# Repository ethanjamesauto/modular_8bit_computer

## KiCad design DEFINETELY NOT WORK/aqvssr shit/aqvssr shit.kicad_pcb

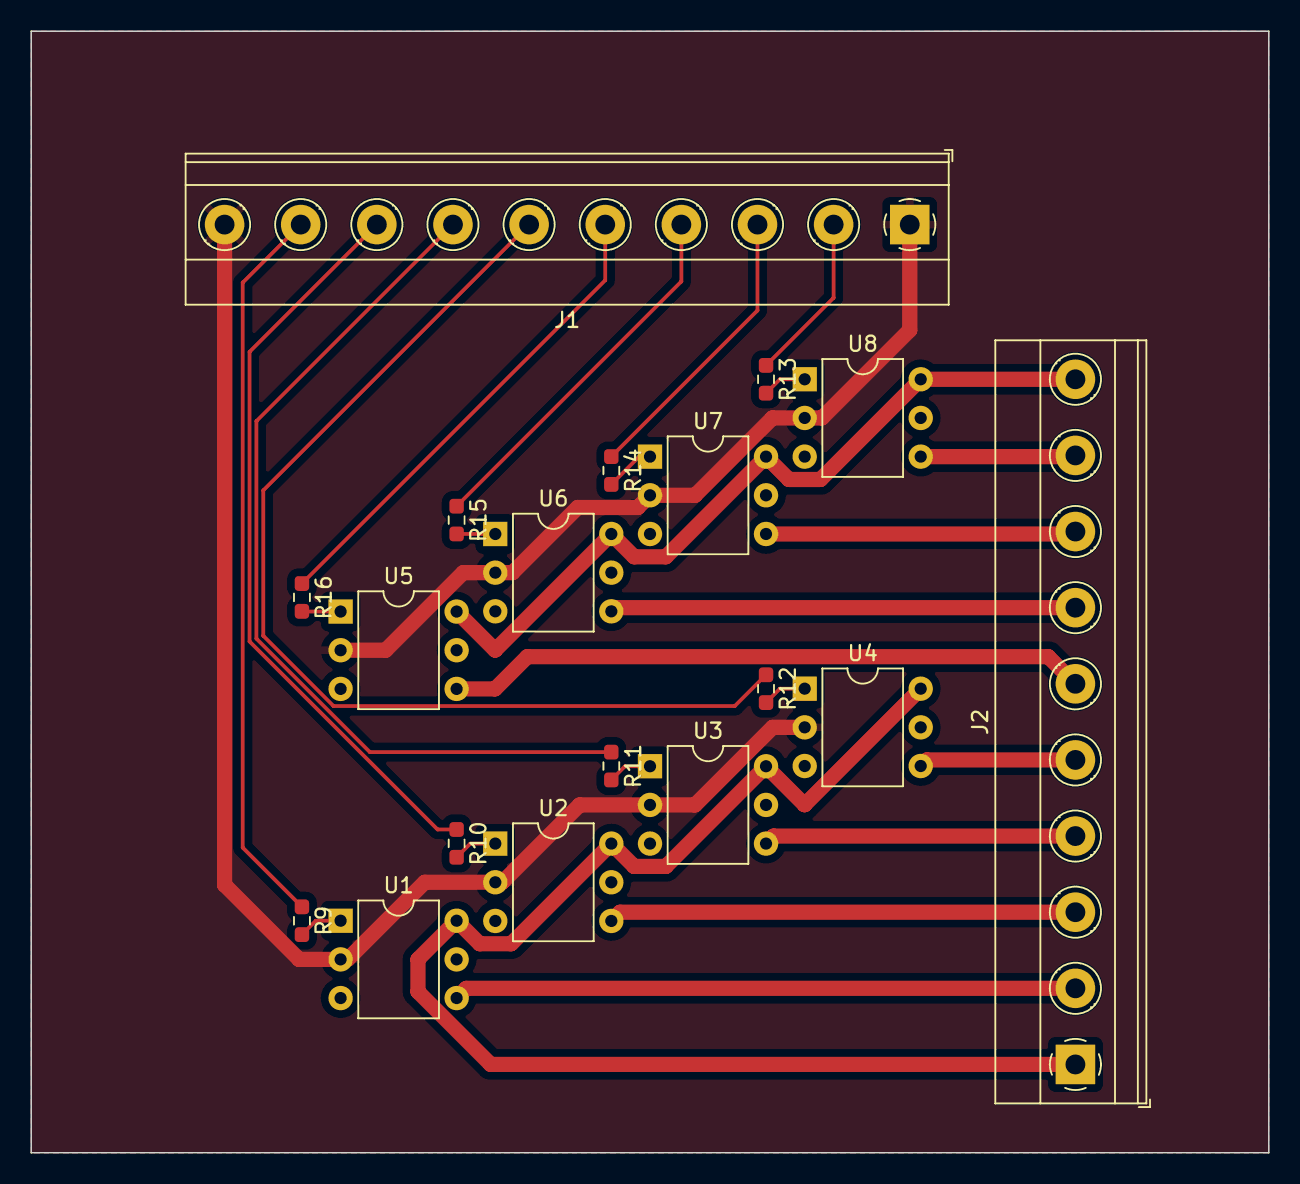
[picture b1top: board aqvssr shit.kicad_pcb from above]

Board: 2 copper layers, 81.3 x 73.7 mm, 18 parts (0 on the bottom side), 26 nets.

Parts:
J1, J2: Conn_01x10_Socket; TerminalBlock_Phoenix_MKDS-1,5-10_1x10_P5.00mm_Horizontal
R9, R10, R11, R12, R13, R14, R15, R16: R; R_0603_1608Metric_Pad0.98x0.95mm_HandSolder
U1, U2, U3, U4, U5, U6, U7, U8: 4N25; DIP-6_W7.62mm

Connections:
/enable_A: J1.9, R9.1
/enable_B: J1.8, R10.1
/enable_C: J1.7, R11.1
/enable_D: J1.6, R12.1
/enable_E: J1.5, R16.1
/enable_F: J1.4, R15.1
/enable_G: J1.3, R14.1
/enable_H: J1.2, R13.1
/hs: J2.1, J2.10, U1.6, U2.6, U3.6, U4.6, U5.6, U6.6, U7.6, U8.6
/ls_A: J2.2, U1.4
/ls_B: J2.3, U2.4
/ls_C: J2.4, U3.4
/ls_D: J2.5, U4.4
/ls_E: J2.6, U5.4
/ls_F: J2.7, U6.4
/ls_G: J2.8, U7.4
/ls_H: J2.9, U8.4
GND: J1.1, J1.10, U1.2, U2.2, U3.2, U4.2, U5.2, U6.2, U7.2, U8.2
unnamed: R9.2, U1.1
unnamed: R10.2, U2.1
unnamed: R11.2, U3.1
unnamed: R12.2, U4.1
unnamed: R13.2, U8.1
unnamed: R14.2, U7.1
unnamed: R15.2, U6.1
unnamed: R16.2, U5.1

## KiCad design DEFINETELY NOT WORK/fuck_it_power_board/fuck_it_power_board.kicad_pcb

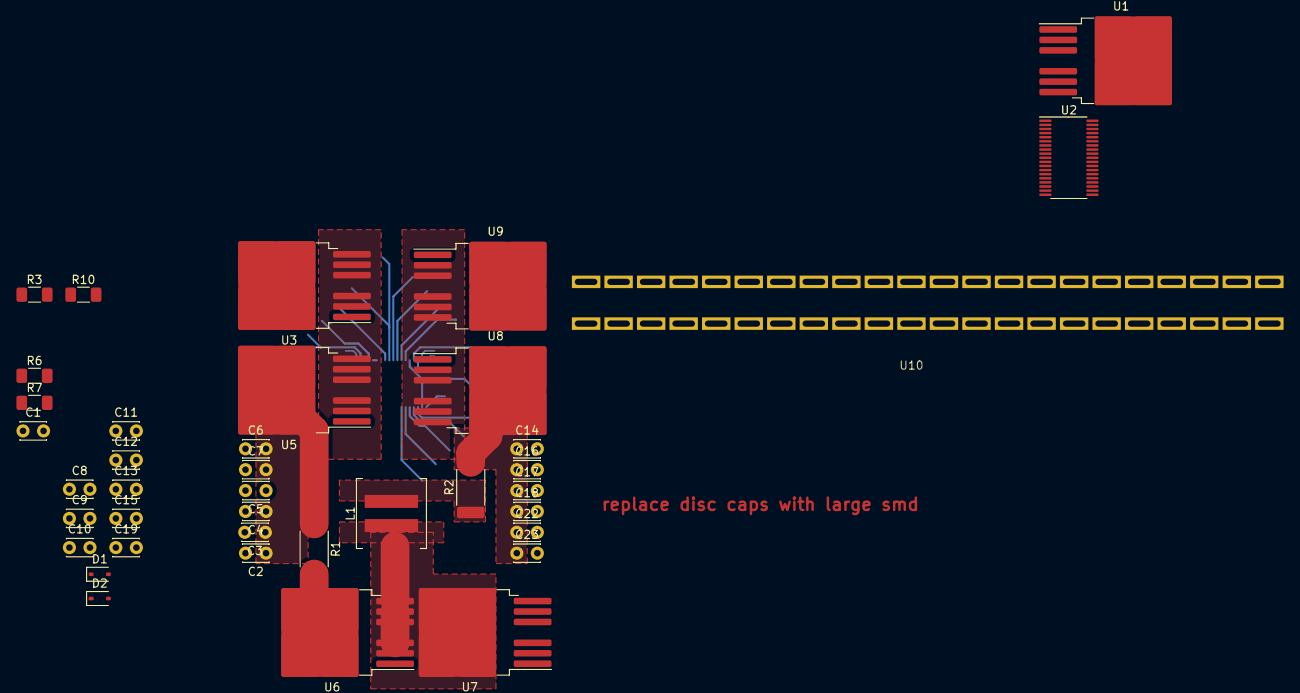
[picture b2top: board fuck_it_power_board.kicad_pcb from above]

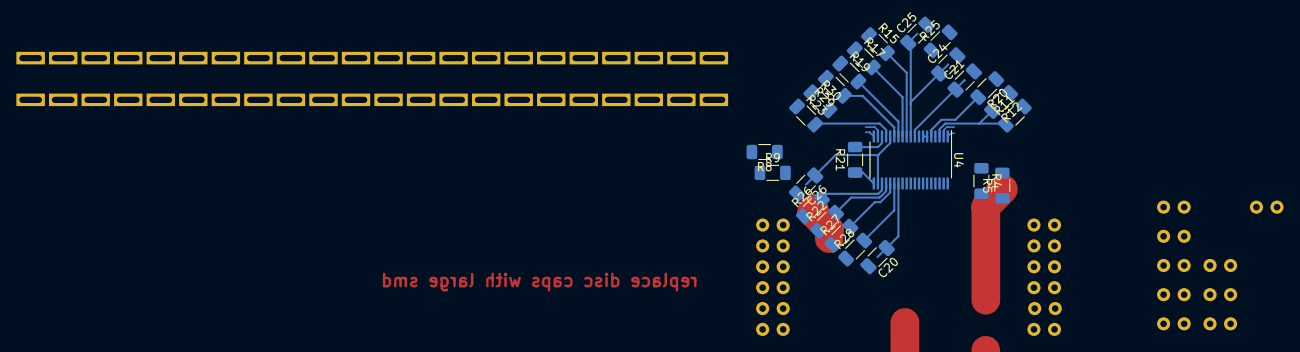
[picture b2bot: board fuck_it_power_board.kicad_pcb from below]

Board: 2 copper layers, 64 parts (25 on the bottom side), 42 nets.

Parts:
C1, C2, C3, C4, C5, C6, C7, C8, C9, C10, C11, C12, C13, C14, C15, C16, C17, C18, C19, C22, C23: C; C_Disc_D3.0mm_W2.0mm_P2.50mm
C20, C21, C24, C25, C26: C; C_1206_3216Metric_Pad1.33x1.80mm_HandSolder
D1: D_TVS; D_SOD-323
D2: D; D_SOD-323
L1: L; L_Coilcraft_XAL7030-472
R1, R2: R; R_2512_6332Metric_Pad1.40x3.35mm_HandSolder
R3, R4, R5, R6, R7, R8, R9, R10, R11, R12, R15, R17, R19, R20, R21, R22, R23, R25, R26, R27, R28, R29, R30: R; R_1206_3216Metric_Pad1.30x1.75mm_HandSolder
U1, U3, U5, U6, U7, U8, U9: TO-263-6
U2, U4: TSSOP-38_4.4x9.7mm_P0.5mm
U10: 50-44A-30

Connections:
/LT8228_BUCK/BG: R7.1, U4.27 (BG)
/LT8228_BUCK/BST: C10.1, D2.1 (K), U4.32 (BST)
/LT8228_BUCK/DG1: D1.2 (A2), R3.2, U3.1, U4.38 (DG1), U5.1
/LT8228_BUCK/DG2: R10.2, U4.35 (DG2), U8.1, U9.1
/LT8228_BUCK/DRVCC: C11.1, D2.2 (A), U4.28 (DRVCC)
/LT8228_BUCK/DRXN: R26.2, U4.22 (DRXN)
/LT8228_BUCK/DS1: D1.1 (A1), U3.2, U3.3, U3.5, U3.6, U3.7, U4.37 (DS1), U5.2, U5.3, U5.5, U5.6, U5.7
/LT8228_BUCK/DS2: U4.34 (DS2), U8.2, U8.3, U8.5, U8.6, U8.7, U9.2, U9.3, U9.5, U9.6, U9.7
/LT8228_BUCK/FB2: R29.1, R30.2, U4.14 (FB2)
/LT8228_BUCK/IGND: R21.1, U4.20 (IGN)
/LT8228_BUCK/IMON1: R20.2, U4.5 (IMON1)
/LT8228_BUCK/IMON2: R19.2, U4.13 (IMON2)
/LT8228_BUCK/INTVCC: C26.1, U4.15 (UV2), U4.21 (INTVCC)
/LT8228_BUCK/ISET1P: C13.1, R15.2, U4.11 (ISET1P)
/LT8228_BUCK/ISET2P: C15.1, R17.2, U4.12 (ISET2P)
/LT8228_BUCK/ISHARE: C19.1, R21.2, U4.17 (ISHARE)
/LT8228_BUCK/POST_RSNS1: C9.1, R1.2, R5.1, U6.4
/LT8228_BUCK/POST_RSNS2: C14.1, C16.1, C17.1, C18.1, C22.1, C23.1, R2.2, R9.1, R29.2, U8.4
/LT8228_BUCK/PRE_RSNS2: L1.2, R2.1, R8.2
/LT8228_BUCK/RT: R23.2, U4.16 (RT)
/LT8228_BUCK/SNS1N: R5.2, U4.2 (SNS1N)
/LT8228_BUCK/SNS1P: R4.1, U4.1 (SNS1P)
/LT8228_BUCK/SNS2N: R9.2, U4.19 (SNS2N)
/LT8228_BUCK/SNS2P: R8.1, U4.18 (SNS2P)
/LT8228_BUCK/SS: C21.1, U4.9 (SS)
/LT8228_BUCK/SW: C10.2, L1.1, U4.30 (SW), U6.2, U6.3, U6.5, U6.6, U6.7, U7.4
/LT8228_BUCK/SYNC: R22.2, U4.23 (SYNC)
/LT8228_BUCK/TG: R6.1, U4.31 (TG)
/LT8228_BUCK/TMR: C20.1, U4.26 (TMR)
/LT8228_BUCK/UV1: R11.1, R12.2, U4.3 (UV1)
/LT8228_BUCK/V1D: C2.1, C3.1, C4.1, C5.2, C6.2, C7.2, R1.1, R4.2, U4.36 (V1D), U5.4
/LT8228_BUCK/VC2: C24.1, C25.1, U4.10 (VC2)
/LT8228_BUCK/~FAULT: R27.2, U4.24 (~FAULT)
/LT8228_BUCK/~REPORT: R28.2, U4.25 (~REPORT)
BUCK_INPUT: C1.1, R11.2, U3.4
GND: C1.2, C2.2, C3.2, C4.2, C5.1, C6.1, C7.1, C8.2, C9.2, C11.2, C12.2, C13.2, C14.2, C15.2, C16.2, C17.2, C18.2, C19.2, C20.2, C21.2, C22.2, C23.2, C25.2, C26.2, R12.1, R15.1, R17.1, R19.1, R20.1, R22.1, R23.1, R25.1, R30.1, U4.4 (FB1), U4.6 (ISET1N), U4.7 (ISET2N), U7.2, U7.3, U7.5, U7.6, U7.7
unnamed: C8.1, R3.1
unnamed: C12.1, R10.1
unnamed: C24.2, R25.2
unnamed: R6.2, U6.1
unnamed: R7.2, U7.1
unnamed: U1.2, U1.3, U1.5, U1.6, U1.7

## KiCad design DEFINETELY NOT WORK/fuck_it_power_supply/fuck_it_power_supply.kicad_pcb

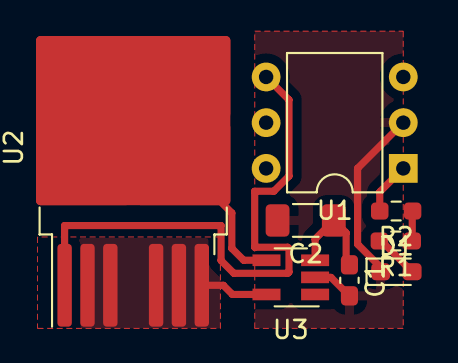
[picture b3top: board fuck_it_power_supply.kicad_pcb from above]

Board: 2 copper layers, 8 parts (0 on the bottom side), 8 nets.

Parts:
C1: C; C_0603_1608Metric_Pad1.08x0.95mm_HandSolder
C2: C; C_1206_3216Metric_Pad1.33x1.80mm_HandSolder
D1: LED; LED_0603_1608Metric_Pad1.05x0.95mm_HandSolder
R1, R2: 470; R_0603_1608Metric_Pad0.98x0.95mm_HandSolder
U1: DIP-6_W7.62mm
U2: TO-263-6
U3: SOT-23-5_HandSoldering

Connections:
/Big Free Load Switch/POWER_INPUT: U2.4, U3.4 (IN+)
/Big Free Load Switch/POWER_OUTPUT: U2.2, U2.3, U2.5, U2.6, U2.7, U3.5 (IN-)
/Big Free Load Switch/close: R1.1, R2.1
/Big Free Load Switch/i_sns_supply: C1.1, C2.1, U3.3 (Vs)
GND: C1.2, C2.2, D1.1 (K), U1.2, U3.2 (GND)
unnamed: D1.2 (A), R1.2
unnamed: R2.2, U1.1
unnamed: U1.4, U2.1

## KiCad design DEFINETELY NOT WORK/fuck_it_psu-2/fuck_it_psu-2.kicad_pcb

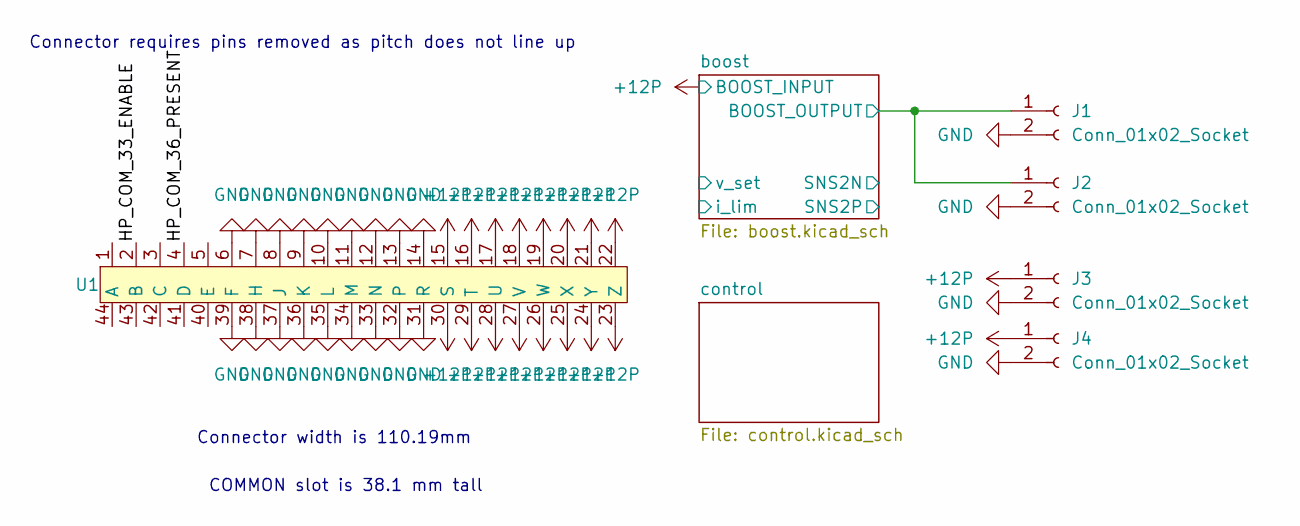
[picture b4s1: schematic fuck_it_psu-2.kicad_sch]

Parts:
J1, J2, J3, J4: Conn_01x02_Socket; PhoenixContact_MSTBA_2,5_2-G_1x02_P5.00mm_Horizontal
U1: 50-44A-30

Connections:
+12P: J3.1, J4.1, U1.15, U1.16, U1.17, U1.18, U1.19, U1.20, U1.21, U1.22, U1.23 (Z), U1.24 (Y), U1.25 (X), U1.26 (W), U1.27 (V), U1.28 (U), U1.29 (T), U1.30 (S); also elsewhere on the board
/HP_COM_33_ENABLE: U1.2
/HP_COM_36_PRESENT: U1.4
/boost/BOOST_OUTPUT: J1.1, J2.1; also elsewhere on the board
GND: J1.2, J2.2, J3.2, J4.2, U1.6, U1.7, U1.8, U1.9, U1.10, U1.11, U1.12, U1.13, U1.14, U1.31 (R), U1.32, U1.33 (N), U1.34 (M), U1.35 (L), U1.36 (K), U1.37 (J), U1.38 (H), U1.39 (F); also elsewhere on the board

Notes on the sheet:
Connector width is 110.19mm
Connector requires pins removed as pitch does not line up
COMMON slot is 38.1 mm tall

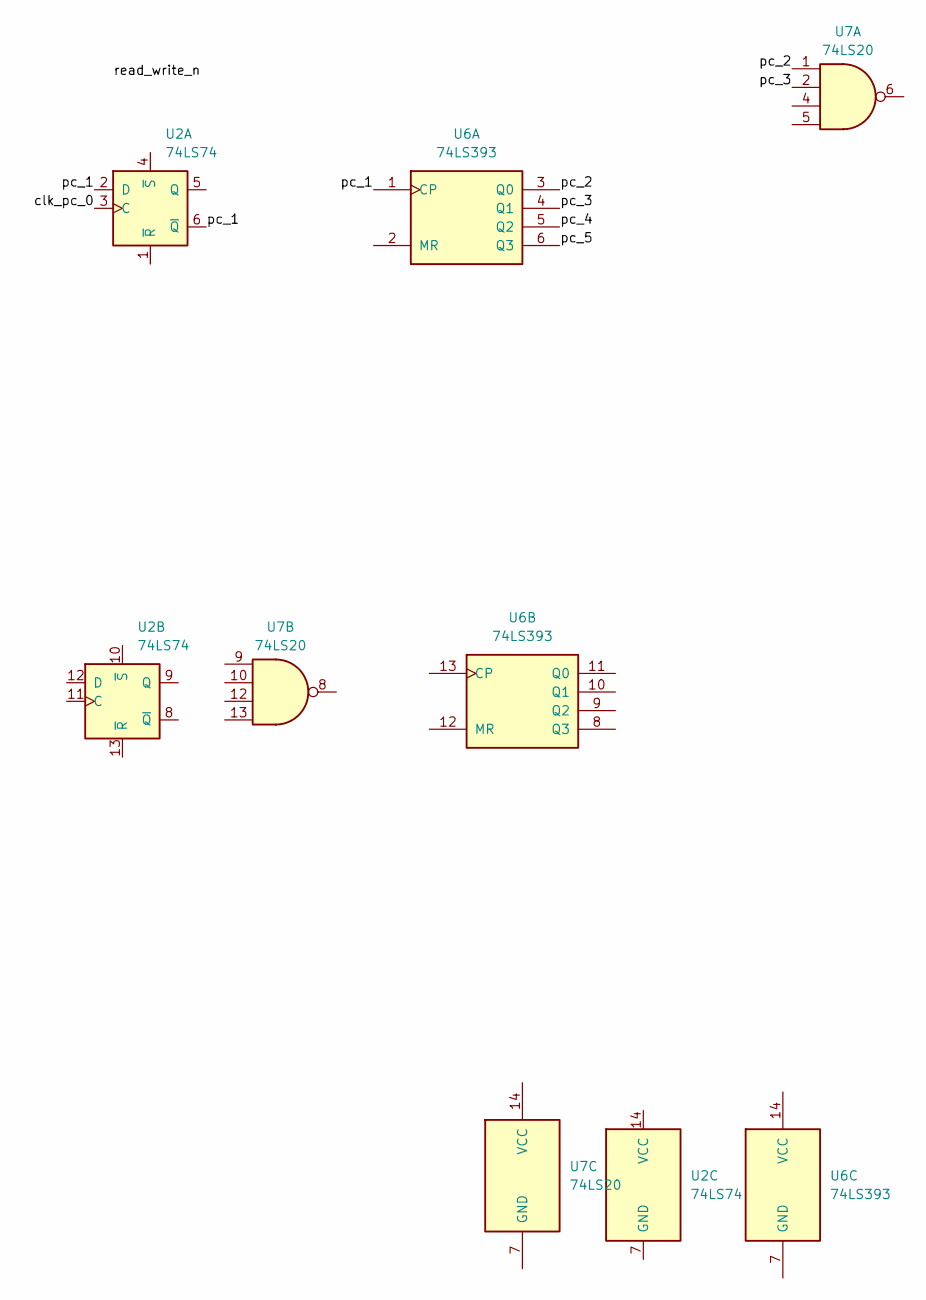
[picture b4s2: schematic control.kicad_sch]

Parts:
U2: 74LS74
U6: 74LS393
U7: 74LS20

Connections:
unnamed: U2.2 (D), U2.6 (~Q), U6.1 (CP)
unnamed: U6.3 (Q0), U7.1
unnamed: U6.4 (Q1), U7.2

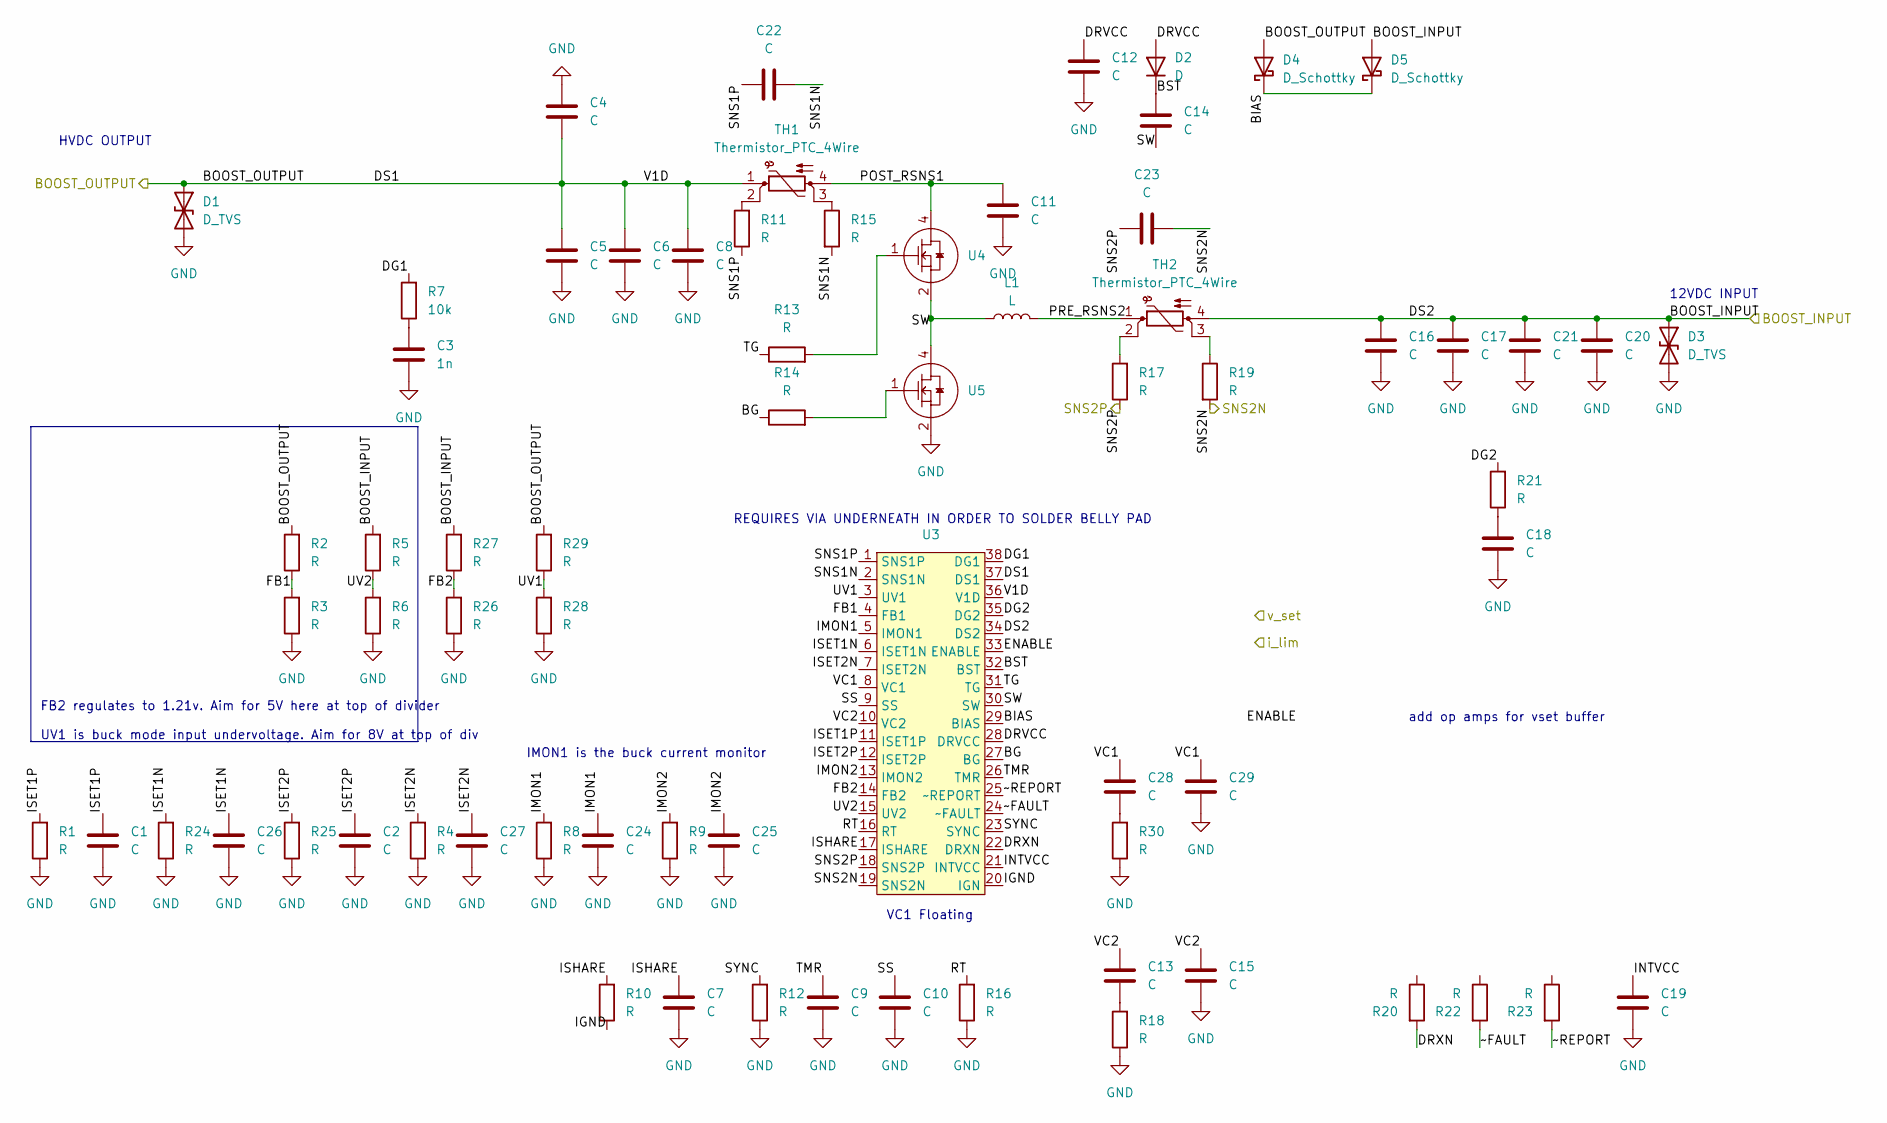
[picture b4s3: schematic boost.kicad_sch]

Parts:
C1, C2, C7, C9, C10, C11, C12, C13, C14, C15, C18, C19, C22, C23, C24, C25, C26, C27, C28, C29: C; C_0603_1608Metric_Pad1.08x0.95mm_HandSolder
C3: 1n; C_0603_1608Metric_Pad1.08x0.95mm_HandSolder
C4, C5, C6, C8, C16, C17, C20, C21: C; C_2220_5650Metric_Pad1.97x5.40mm_HandSolder
D1, D3: D_TVS; D_1206_3216Metric_Pad1.42x1.75mm_HandSolder
D2: D; D_1206_3216Metric_Pad1.42x1.75mm_HandSolder
D4, D5: D_Schottky; D_1206_3216Metric_Pad1.42x1.75mm_HandSolder
L1: L; L_Coilcraft_XAL1580-102
R1, R2, R3, R4, R5, R6, R8, R9, R10, R11, R12, R13, R14, R15, R16, R17, R18, R19, R20, R21, R22, R23, R24, R25, R26, R27, R28, R29, R30: R; R_0603_1608Metric_Pad0.98x0.95mm_HandSolder
R7: 10k; R_0603_1608Metric_Pad0.98x0.95mm_HandSolder
TH1, TH2: Thermistor_PTC_4Wire; R_Shunt_Vishay_WSKW0612
U3: TSSOP-38_4.4x9.7mm_P0.5mm
U4, U5: TO-263-6

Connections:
+12P: C16.1, C17.1, C20.1, C21.1, D3.1 (A1), D5.2 (A), R5.2, R27.2, TH2.4, U3.34 (DS2); also elsewhere on the board
/boost/BG: R14.1, U3.27 (BG)
/boost/BIAS: D4.1 (K), D5.1 (K), U3.29 (BIAS)
/boost/BOOST_OUTPUT: C4.2, C5.1, C6.1, C8.1, D1.1 (A1), D4.2 (A), R2.2, R29.2, TH1.1, U3.36 (V1D), U3.37 (DS1); also elsewhere on the board
/boost/BST: C14.1, D2.1 (K), U3.32 (BST)
/boost/DG1: R7.2, U3.38 (DG1)
/boost/DG2: R21.2, U3.35 (DG2)
/boost/DRVCC: C12.1, D2.2 (A), U3.28 (DRVCC)
/boost/DRXN: R20.2, U3.22 (DRXN)
/boost/ENABLE: U3.33 (ENABLE)
/boost/FB1: R2.1, R3.2, U3.4 (FB1)
/boost/FB2: R26.2, R27.1, U3.14 (FB2)
/boost/IGND: R10.1, U3.20 (IGN)
/boost/IMON1: C24.1, R8.2, U3.5 (IMON1)
/boost/IMON2: C25.1, R9.2, U3.13 (IMON2)
/boost/INTVCC: C19.1, U3.21 (INTVCC)
/boost/ISET1N: C26.1, R24.2, U3.6 (ISET1N)
/boost/ISET1P: C1.1, R1.2, U3.11 (ISET1P)
/boost/ISET2N: C27.1, R4.2, U3.7 (ISET2N)
/boost/ISET2P: C2.1, R25.2, U3.12 (ISET2P)
/boost/ISHARE: C7.1, R10.2, U3.17 (ISHARE)
/boost/POST_RSNS1: C11.1, TH1.4, U4.4
/boost/PRE_RSNS2: L1.2, TH2.1
/boost/RT: R16.2, U3.16 (RT)
/boost/SNS1N: C22.2, R15.2, U3.2 (SNS1N)
/boost/SNS1P: C22.1, R11.1, U3.1 (SNS1P)
/boost/SNS2N: C23.2, R19.2, U3.19 (SNS2N)
/boost/SNS2P: C23.1, R17.1, U3.18 (SNS2P)
/boost/SS: C10.1, U3.9 (SS)
/boost/SW: C14.2, L1.1, U3.30 (SW), U4.2, U4.3, U4.5, U4.6, U4.7, U5.4
/boost/SYNC: R12.2, U3.23 (SYNC)
/boost/TG: R13.1, U3.31 (TG)
/boost/TMR: C9.1, U3.26 (TMR)
/boost/UV1: R28.2, R29.1, U3.3 (UV1)
/boost/UV2: R5.1, R6.2, U3.15 (UV2)
/boost/VC1: C28.1, C29.1, U3.8 (VC1)
/boost/VC2: C13.1, C15.1, U3.10 (VC2)
/boost/~FAULT: R22.2, U3.24 (~FAULT)
/boost/~REPORT: R23.2, U3.25 (~REPORT)
GND: C1.2, C2.2, C3.2, C4.1, C5.2, C6.2, C7.2, C8.2, C9.2, C10.2, C11.2, C12.2, C15.2, C16.2, C17.2, C18.2, C19.2, C20.2, C21.2, C24.2, C25.2, C26.2, C27.2, C29.2, D1.2 (A2), D3.2 (A2), R1.1, R3.1, R4.1, R6.1, R8.1, R9.1, R12.1, R16.1, R18.1, R24.1, R25.1, R26.1, R28.1, R30.1, U5.2, U5.3, U5.5, U5.6, U5.7; also elsewhere on the board
unnamed: C3.1, R7.1
unnamed: C13.2, R18.2
unnamed: C18.1, R21.1
unnamed: C28.2, R30.2
unnamed: R11.2, TH1.2
unnamed: R13.2, U4.1
unnamed: R14.2, U5.1
unnamed: R15.1, TH1.3
unnamed: R17.2, TH2.2
unnamed: R19.1, TH2.3

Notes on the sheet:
IMON1 is the buck current monitor
REQUIRES VIA UNDERNEATH IN ORDER TO SOLDER BELLY PAD
HVDC OUTPUT
VC1 Floating
FB2 regulates to 1.21v. Aim for 5V here at top of divider UV1 is buck mode input undervoltage. Aim for 8V at top of div
add op amps for vset buffer
12VDC INPUT

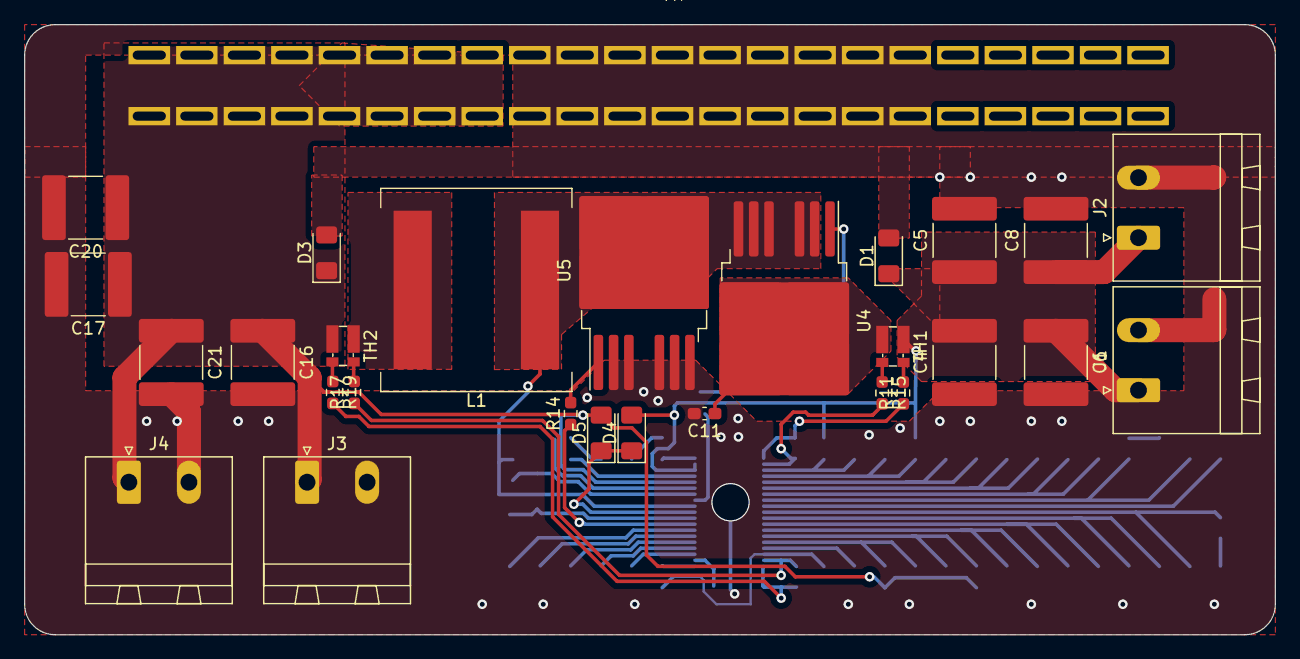
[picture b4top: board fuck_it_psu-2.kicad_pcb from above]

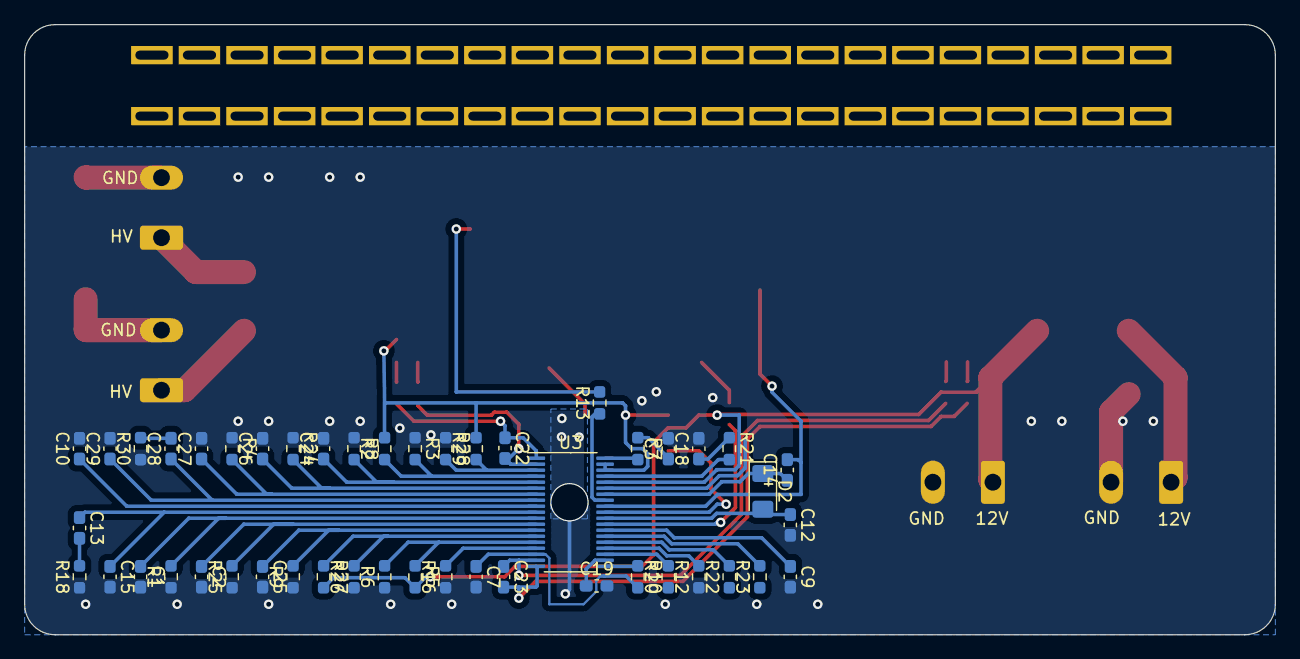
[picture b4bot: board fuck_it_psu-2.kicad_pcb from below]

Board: 2 copper layers, 104.1 x 50.8 mm, 75 parts (47 on the bottom side), 49 nets.

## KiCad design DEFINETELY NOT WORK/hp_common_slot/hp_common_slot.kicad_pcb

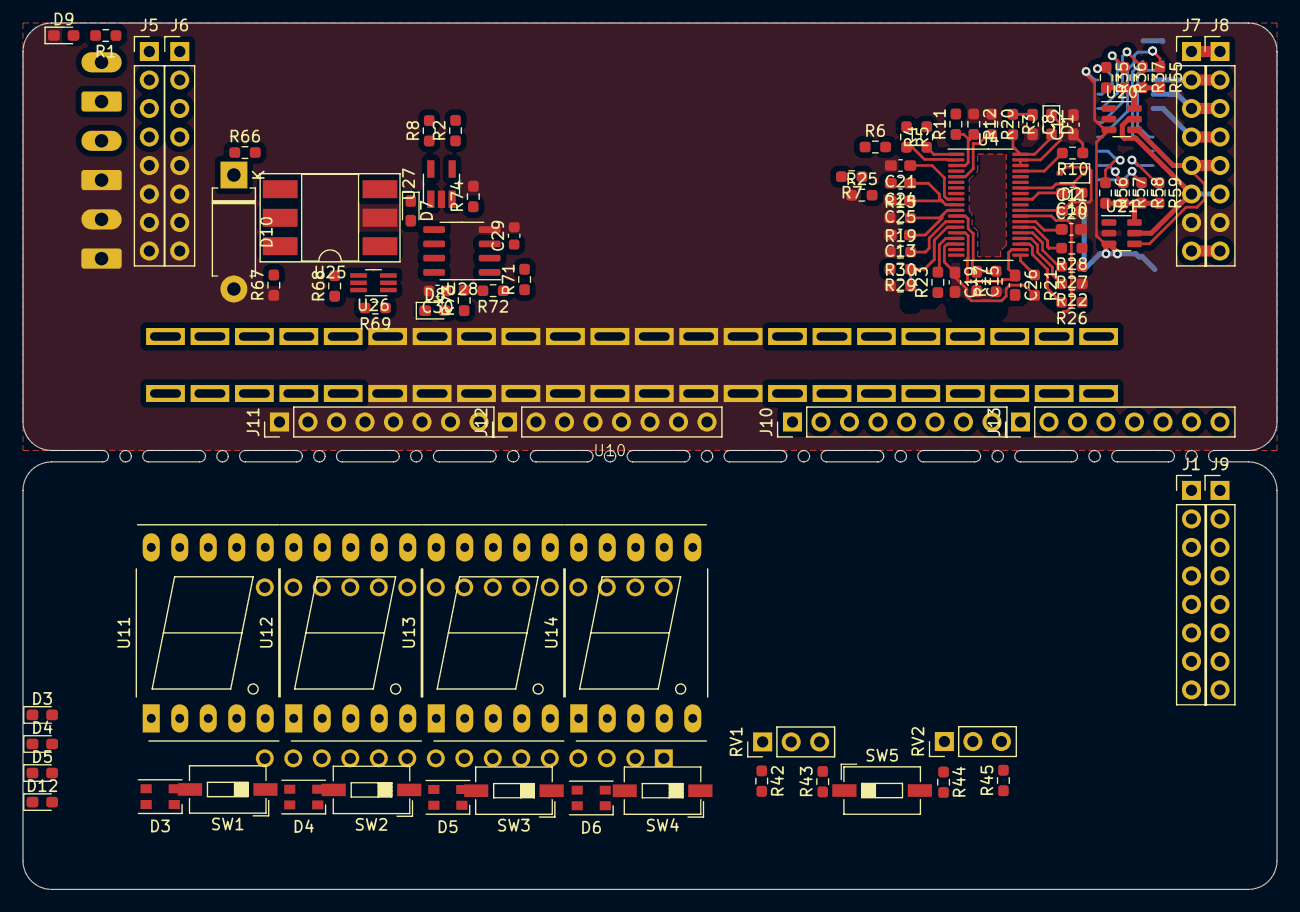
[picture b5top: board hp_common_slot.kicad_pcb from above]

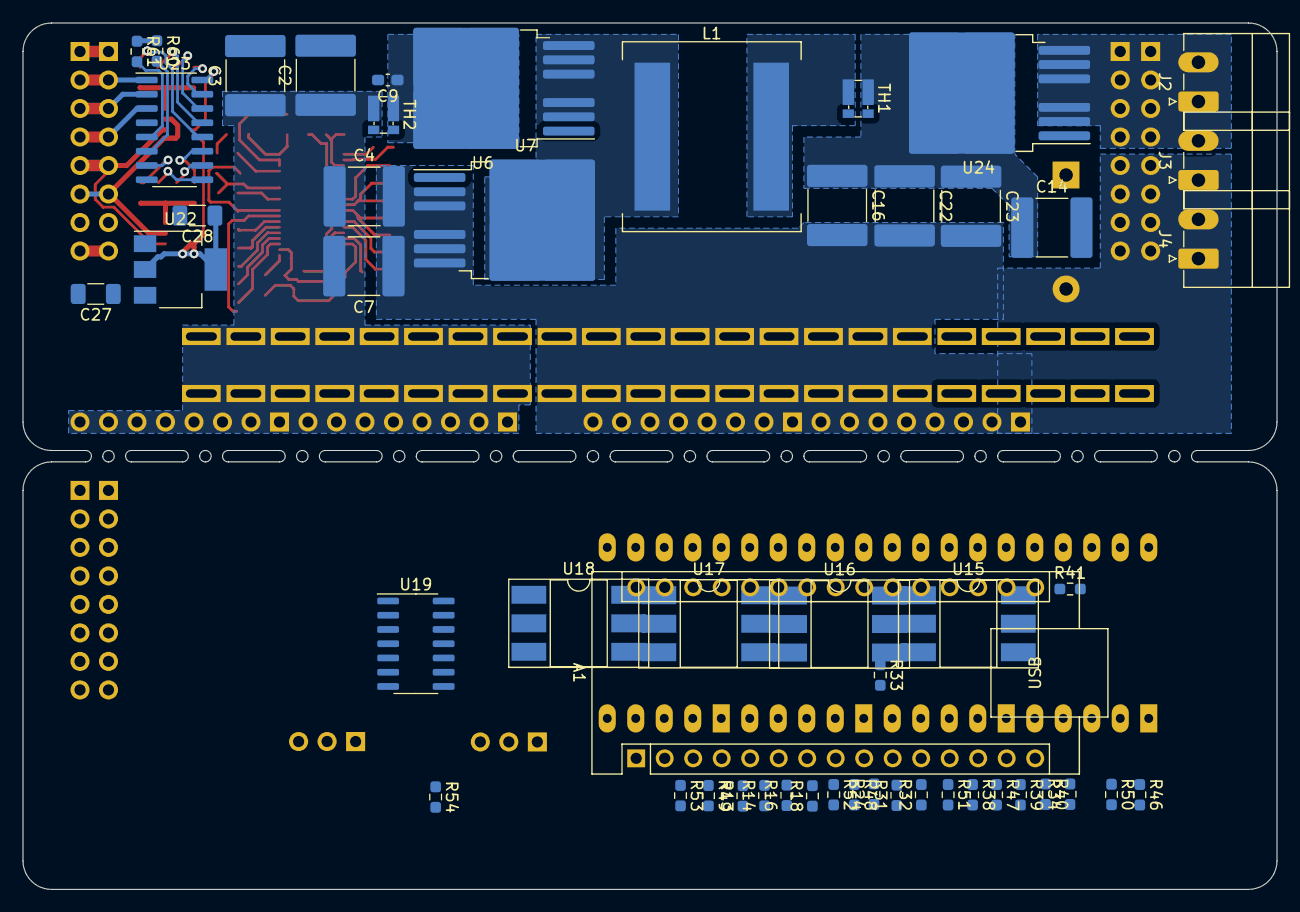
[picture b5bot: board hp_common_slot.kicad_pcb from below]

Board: 2 copper layers, 111.8 x 77.2 mm, 153 parts (52 on the bottom side), 130 nets.

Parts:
A1: Arduino_Nano_Every; Arduino_Nano
C2, C3, C4, C7, C14, C16, C22, C23: C; C_2220_5650Metric_Pad1.97x5.40mm_HandSolder
C8, C9, C10, C11, C12, C13, C15, C19, C20, C21, C24, C25, C26: C; C_0603_1608Metric_Pad1.08x0.95mm_HandSolder
C27, C28: 1uF; C_1206_3216Metric_Pad1.33x1.80mm_HandSolder
C29, C30: C; C_0603_1608Metric
D1: D_TVS; D_0603_1608Metric_Pad1.05x0.95mm_HandSolder
D2: D; D_SOD-323
D3, D4#2, D5, D6: LED_RABG; LED_Cree-PLCC4_3.2x2.8mm_CCW
D3#2, D4, D5#2, D9, D12: LED; LED_0603_1608Metric_Pad1.05x0.95mm_HandSolder
D7, D8: D; D_0603_1608Metric_Pad1.05x0.95mm_HandSolder
D10: D_TVS; D_DO-15_P10.16mm_Horizontal
J1, J5, J6, J7, J8, J9, J10, J11, J12, J13: Conn_01x08_Pin; PinHeader_1x08_P2.54mm_Vertical
J2, J3, J4: Conn_01x02_Socket; PhoenixContact_MC_1,5_2-G-3.5_1x02_P3.50mm_Horizontal
L1: L; L_Coilcraft_XAL1580-102
R1, R2, R3, R4, R5, R6, R7, R8, R10, R11, R12, R13, R14, R15, R16, R17, R18, R19, R20, R21, R22, R23, R24, R25, R26, R27, R28, R29, R30, R31, R32, R33, R34, R35, R36, R37, R38, R39, R40, R41, R42, R43, R44, R45, R46, R47, R48, R49, R50, R51, R52, R53, R54, R55, R56, R57, R58, R59, R60, R61, R66, R67, R68, R69, R71, R72, R73, R74: R; R_0603_1608Metric_Pad0.98x0.95mm_HandSolder
RV1, RV2: R_Potentiometer; PinHeader_1x03_P2.54mm_Vertical
SW1, SW2, SW3, SW4, SW5: SW_Push; SW_DIP_SPSTx01_Slide_6.7x4.1mm_W6.73mm_P2.54mm_LowProfile_J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
TH1, TH2: Thermistor_PTC_4Wire; R_Shunt_Vishay_WSKW0612
U4: TSSOP-38_4.4x9.7mm_P0.5mm
U6, U7, U24: TO-263-6
U10: 50-44A-30
U11, U12, U13, U14: SM420561N; 7SegmentLED_LTS6760_LTS6780
U15, U16, U17, U18, U25: DIP-6_W8.89mm_SMDSocket_LongPads
U19: 74HC00; SOIC-14_3.9x8.7mm_P1.27mm
U20, U21: MCP4725xxx-xCH; SOT-23-6
U22: SOT-223-3_TabPin2
U23: 74LS138; SOIC-16_3.9x9.9mm_P1.27mm
U26: 74LVC1G11; SOT-363_SC-70-6_Handsoldering
U27: SOT-23-5_HandSoldering
U28: LM358; SOIC-8_3.9x4.9mm_P1.27mm

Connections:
+5P: C28.1, U20.3 (VDD), U21.3 (VDD), U22.2 (VOUT), U23.16 (VCC)
+12P: C2.1, C3.1, C4.1, C7.2, D1.1 (A1), J10.1, J10.2, J10.3, J10.4, J10.5, J10.6, J10.7, J10.8, J13.1, J13.2, J13.3, J13.4, J13.5, J13.6, J13.7, J13.8, R11.2, TH2.4, U4.36 (V1D), U4.37 (DS1), U10.15, U10.16, U10.17, U10.18, U10.19, U10.20, U10.21, U10.22, U10.23 (Z), U10.24 (Y), U10.25 (X), U10.26 (W), U10.27 (V), U10.28 (U), U10.29 (T), U10.30 (S)
+12V: C27.1, J1.8, J7.8, J8.8, J9.8, U22.3 (VIN)
/Controller/3v3_nano: A1.17 (3V3), A1.18 (AREF)
/Controller/5v_nano: A1.27 (+5V), R54.2, U15.6, U16.6, U17.6, U18.6, U19.14 (VCC)
/Controller/button_rtn: A1.12 (D9), R34.2, SW1.1, SW2.1, SW3.1, SW4.1
/Controller/dac_scl: A1.24 (SCL/A5), J1.6, J9.6
/Controller/dac_sda: A1.23 (SDA/A4), J1.5, J9.5
/Controller/digit_0_enable: A1.13 (D10), R38.1
/Controller/digit_0_supply: D3.2 (A), D3#2.2 (A), R42.2, SW1.2, U11.3 (CC), U11.8 (CC), U15.4
/Controller/digit_1_enable: A1.14 (MOSI), R39.1
/Controller/digit_1_supply: D4.2 (A), D4#2.2 (A), R44.2, SW2.2, U12.3 (CC), U12.8 (CC), U16.4
/Controller/digit_2_enable: A1.15 (MISO), R40.1
/Controller/digit_2_supply: D5.2 (A), D5#2.2 (A), SW3.2, U13.3 (CC), U13.8 (CC), U17.4
/Controller/digit_3_enable: A1.16 (SCK), R41.1
/Controller/digit_3_supply: D6.2 (A), D12.2 (A), SW4.2, U14.3 (CC), U14.8 (CC), U18.4
/Controller/enable_led: A1.20 (A1), R46.1, R47.1, R48.1, R49.1, U19.2, U19.5, U19.10, U19.13
/Controller/extra_analog: A1.26 (A7), J1.1, J9.1
/Controller/knob: A1.19 (A0), RV1.2, RV2.2
/Controller/sev_seg_A: R13.1, U11.7 (A), U12.7 (A), U13.7 (A), U14.7 (A)
/Controller/sev_seg_A_sink: A1.5 (D2), R13.2
/Controller/sev_seg_B: R14.1, U11.6 (B), U12.6 (B), U13.6 (B), U14.6 (B)
/Controller/sev_seg_B_sink: A1.6 (D3), R14.2
/Controller/sev_seg_C: R16.1, U11.4 (C), U12.4 (C), U13.4 (C), U14.4 (C)
/Controller/sev_seg_C_sink: A1.7 (D4), R16.2
/Controller/sev_seg_D: R18.1, U11.2 (D), U12.2 (D), U13.2 (D), U14.2 (D)
/Controller/sev_seg_D_sink: A1.8 (D5), R18.2
/Controller/sev_seg_E: R24.1, U11.1 (E), U12.1 (E), U13.1 (E), U14.1 (E)
/Controller/sev_seg_E_sink: A1.9 (D6), R24.2
/Controller/sev_seg_F: R31.1, U11.9 (F), U12.9 (F), U13.9 (F), U14.9 (F)
/Controller/sev_seg_F_sink: A1.10 (D7), R31.2
/Controller/sev_seg_G: R32.1, U11.10 (G), U12.10 (G), U13.10 (G), U14.10 (G)
/Controller/sev_seg_G_sink: A1.11 (D8), R32.2
/Controller/supply_channel_0_fault_n: R50.1, U19.1
/Controller/supply_channel_1_fault_n: R51.1, U19.4
/Controller/supply_channel_2_fault_n: R52.1, U19.9
/Controller/supply_channel_3_fault_n: R53.1, U19.12
/Controller/supply_channel_addr_0: A1.21 (A2), J1.2, J9.2
/Controller/supply_channel_addr_1: A1.22 (A3), J1.3, J9.3
/Controller/supply_channel_addr_2: A1.25 (A6), J1.4, J9.4
/LT8228_BUCK/BG: R7.1, U4.27 (BG)
/LT8228_BUCK/BST: C10.1, D2.1 (K), U4.32 (BST)
/LT8228_BUCK/BUCK_OUTPUT: C14.1, C16.1, C22.1, C23.1, D10.1 (A1), TH1.1, U4.34 (DS2), U24.4
/LT8228_BUCK/DG1: D1.2 (A2), R3.2, U4.38 (DG1)
/LT8228_BUCK/DG2: R10.2, U4.35 (DG2)
/LT8228_BUCK/DRVCC: C11.1, D2.2 (A), U4.28 (DRVCC)
/LT8228_BUCK/DRXN: R26.2, U4.22 (DRXN)
/LT8228_BUCK/FB2: R29.1, R30.2, U4.14 (FB2)
/LT8228_BUCK/IGND: R21.1, U4.20 (IGN)
/LT8228_BUCK/IMON1: R20.2, U4.5 (IMON1)
/LT8228_BUCK/IMON2: R19.2, U4.13 (IMON2)
/LT8228_BUCK/INTVCC: C26.1, U4.15 (UV2), U4.21 (INTVCC)
/LT8228_BUCK/ISET1P: C13.1, R15.2, U4.11 (ISET1P)
/LT8228_BUCK/ISET2P: C15.1, R17.2, U4.12 (ISET2P)
/LT8228_BUCK/ISHARE: C19.1, R21.2, U4.17 (ISHARE)
/LT8228_BUCK/POST_RSNS1: C9.1, TH2.1, U6.4
/LT8228_BUCK/PRE_RSNS2: L1.2, TH1.4
/LT8228_BUCK/RT: R23.2, U4.16 (RT)
/LT8228_BUCK/SNS1N: R5.2, U4.2 (SNS1N)
/LT8228_BUCK/SNS1P: R4.1, U4.1 (SNS1P)
/LT8228_BUCK/SNS2N: R8.1, R8.2, TH1.2, U4.19 (SNS2N), U27.5 (IN-)
/LT8228_BUCK/SNS2P: R2.1, R2.2, TH1.3, U4.18 (SNS2P), U27.4 (IN+)
/LT8228_BUCK/SS: C21.1, U4.9 (SS)
/LT8228_BUCK/SW: C10.2, L1.1, U4.30 (SW), U6.2, U6.3, U6.5, U6.6, U6.7, U7.4
/LT8228_BUCK/SYNC: R22.2, U4.23 (SYNC)
/LT8228_BUCK/TG: R6.1, U4.31 (TG)
/LT8228_BUCK/TMR: C20.1, U4.26 (TMR)
/LT8228_BUCK/UV1: R11.1, R12.2, U4.3 (UV1)
/LT8228_BUCK/VC2: C24.1, C25.1, U4.10 (VC2)
/LT8228_BUCK/~FAULT: R27.2, U4.24 (~FAULT)
/LT8228_BUCK/~REPORT: R28.2, U4.25 (~REPORT)
/Load Switch/5p: U26.5 (VCC), U27.3 (Vs), U28.8 (V+)
/Load Switch/close: R68.1, R69.2, U26.4
/Load Switch/enable: D8.1 (K), U26.6
/Load Switch/gate: R66.1, R67.2, U24.1
/Load Switch/i_sns_buffer: R72.1, U28.1, U28.2 (-)
/Load Switch/isns: D7.1 (K), R74.1, U27.1 (OUT), U28.5 (+)
/Load Switch/latch: C30.1, D7.2 (A), R69.1, R73.2, U26.1, U28.7
/Load Switch/reset: D8.2 (A), R73.1
/SUPPLY_POWER_OUT: J2.1, J2.2, J3.2, J5.1, J5.2, J5.3, J5.4, J6.1, J6.2, J6.3, J6.4, R1.1, U24.2, U24.3, U24.5, U24.6, U24.7
/extra_analog: J7.1, J8.1
/i_ao: R56.2, R57.2, R58.2, R59.2, U21.6 (A0)
/supply_addr_0: J7.2, J8.2, U23.1 (A0)
/supply_addr_1: J7.3, J8.3, U23.2 (A1)
/supply_addr_2: J7.4, J8.4, U23.3 (A2)
/supply_addr_en: R60.1, R61.1
/supply_scl: J7.6, J8.6, U20.5 (SCL), U21.5 (SCL)
/supply_sda: J7.5, J8.5, U20.4 (SDA), U21.4 (SDA)
/v_a0: R35.2, R36.2, R37.2, R55.2, U20.6 (A0)
GND: A1.4 (GND), A1.29 (GND), C2.2, C3.2, C4.2, C7.1, C8.2, C9.2, C11.2, C12.2, C13.2, C14.2, C15.2, C16.2, C19.2, C20.2, C21.2, C22.2, C23.2, C25.2, C26.2, C27.2, C28.2, C29.2, C30.2, D9.1 (K), D10.2 (A2), J1.7, J3.1, J4.1, J4.2, J5.5, J5.6, J5.7, J5.8, J6.5, J6.6, J6.7, J6.8, J7.7, J8.7, J9.7, J11.1, J11.2, J11.3, J11.4, J11.5, J11.6, J11.7, J11.8, J12.1, J12.2, J12.3, J12.4, J12.5, J12.6, J12.7, J12.8, R12.1, R15.1, R17.1, R19.1, R20.1, R22.1, R23.1, R25.1, R30.1, R33.1, R34.1, R43.1, R45.1, R67.1, R74.2, SW5.2, U4.4 (FB1), U4.6 (ISET1N), U4.7 (ISET2N), U7.2, U7.3, U7.5, U7.6, U7.7, U10.6, U10.7, U10.8, U10.9, U10.10, U10.11, U10.12, U10.13, U10.14, U10.31 (R), U10.32, U10.33 (N), U10.34 (M), U10.35 (L), U10.36 (K), U10.37 (J), U10.38 (H), U10.39 (F), U15.2, U16.2, U17.2, U18.2, U19.7 (GND), U20.2 (VSS), U21.2 (VSS), U22.1 (GND), U23.4 (E1), U23.8 (GND), U25.2, U26.2 (GND), U27.2 (GND), U28.4 (V-)
unnamed: A1.3 (~RESET), A1.28 (~RESET), R54.1, SW5.1
unnamed: C8.1, R3.1
unnamed: C12.1, R10.1
unnamed: C24.2, R25.2
unnamed: D3#2.1 (K), R46.2
unnamed: D3.1 (RK), R50.2
unnamed: D4.1 (K), R47.2
unnamed: D4#2.1 (RK), R51.2
unnamed: D5#2.1 (K), R48.2
unnamed: D5.1 (RK), R52.2
unnamed: D6.1 (RK), R53.2
unnamed: D9.2 (A), R1.2
unnamed: D12.1 (K), R49.2
unnamed: R4.2, TH2.3
unnamed: R5.1, TH2.2
unnamed: R6.2, U6.1
unnamed: R7.2, U7.1
unnamed: R38.2, U15.1
unnamed: R39.2, U16.1
unnamed: R40.2, U17.1
unnamed: R41.2, U18.1
unnamed: R42.1, RV1.1
unnamed: R43.2, RV1.3
unnamed: R44.1, RV2.1
unnamed: R45.2, RV2.3
unnamed: R66.2, U25.4
unnamed: R68.2, U25.1
unnamed: R33.2, U12.5 (DP)
unnamed: R61.2, U23.5 (E2)
unnamed: R60.2, U23.6 (E3)
unnamed: R35.1, U23.15 (O0)
unnamed: R36.1, U23.14 (O1)
unnamed: R37.1, U23.13 (O2)
unnamed: R55.1, U23.12 (O3)
unnamed: R56.1, U23.11 (O4)
unnamed: R57.1, U23.10 (O5)
unnamed: R58.1, U23.9 (O6)
unnamed: R59.1, U23.7 (O7)
unnamed: C29.1, R71.2, U28.3 (+)
unnamed: R72.2, U28.6 (-)
